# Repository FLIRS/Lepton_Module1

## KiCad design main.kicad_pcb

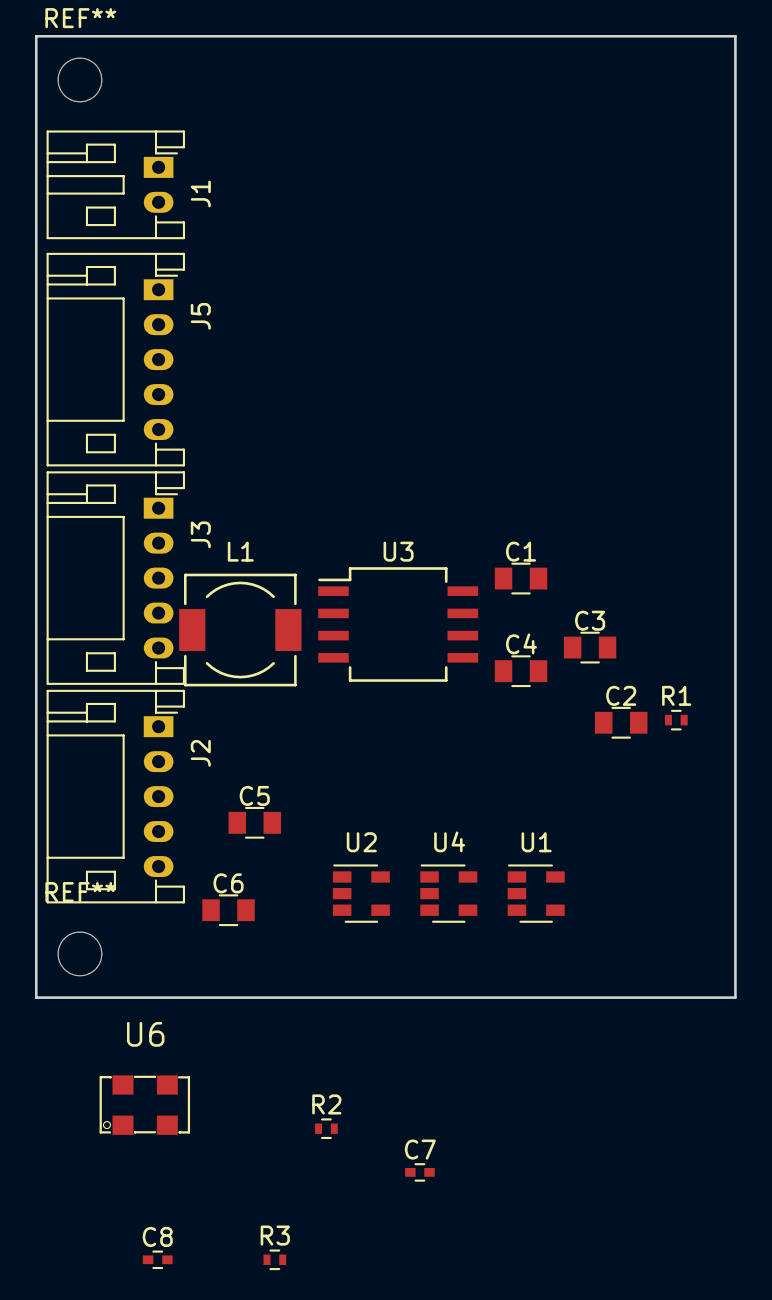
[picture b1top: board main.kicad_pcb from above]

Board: 2 copper layers, 40.0 x 55.0 mm, 22 parts (1 on the bottom side), 24 nets, no tracks yet.

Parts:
C1, C2, C3, C4, C5, C6: C; C_0805
C7, C8: C; C_0402
J1: Conn_01x02; JST_PH_S2B-PH-K_02x2.00mm_Angled
J2, J3, J5: Conn_01x05; JST_PH_S5B-PH-K_05x2.00mm_Angled
L1: L; Choke_SMD_6.3x6.3_H3
R1, R2, R3: R; R_0402
U1, U4: MIC5219-2.8; SOT-23-5
U2: LM3670MF; SOT-23-5
U3: PCA9515A; SO-8_5.3x6.2mm_Pitch1.27mm
U5: FLIR_Lepton; FLIR_Lepton_1050281001
U6: ASFLMB

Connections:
/1.2V: C4.1, L1.1, U2.4, U5.7
/2.8V: C2.1, U1.5, U5.19
/2.8V_IO: C6.1, C7.1, U4.5, U5.16, U6.1, U6.4
/GPIO3: J2.4, U5.2
/I2C_SCL: J2.2, U3.2
/I2C_SDA: J2.1, U3.3
/MIPI_CLK_N: J5.4, U5.28
/MIPI_CLK_P: J5.3, U5.29
/MIPI_DATA_N: J5.2, U5.31
/MIPI_DATA_P: J5.1, U5.32
/SPI_CLK: J3.2, U5.13
/SPI_CS: J3.1, U5.14
/SPI_MISO: J3.3, U5.12
/SPI_MOSI: J3.4, U5.11
GND: C1.2, C2.2, C3.2, C4.2, C5.2, C6.2, C7.2, C8.2, J1.2, J2.5, J3.5, J5.5, U1.2, U2.2, U3.4, U4.2, U5.1, U5.6, U5.8, U5.9, U5.10, U5.15, U5.18, U5.20, U5.25, U5.27, U5.30, U6.2
unnamed: C8.1, R2.2, U5.23
unnamed: L1.2, U2.5
unnamed: R1.2, U3.5
unnamed: R2.1, R3.2
unnamed: R3.1, U5.24
unnamed: U3.6, U5.22
unnamed: U3.7, U5.21
unnamed: U5.26, U6.3
VCC: C1.1, C3.1, C5.1, J1.1, R1.1, U1.1, U1.3, U2.1, U2.3, U3.8, U4.1, U4.3

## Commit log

2017-10-02 test
